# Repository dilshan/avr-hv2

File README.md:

AVR High Voltage Programmer 2
==========================

*AVR-HV2* is *Arduino* based high voltage parallel programmer for *[AVR](https://www.microchip.com/design-centers/8-bit/avr-mcus)* microcontrollers. This programmer can read, write, and erase both flash memory and EEPROM. Also, this can use to set fuse bits of *AVR* MCUs. 

*AVR-HV2* programmer is designed as an *[Arduino Mega](https://www.arduino.cc/en/Main/ArduinoBoardMega2560)* shield. Dimensions of the *AVR-HV2* are similar to the *Arduino Mega* board. It can be powered using a power source connected to the *Arduino Mega* board. The suggested power source for this programmer is a 12V 1A DC power adapter. 

The control software of this programmer is design to work on both *Windows* and *Linux* operating systems. It supports the import and export of memory data in the Intel hex file format. The communication link between the programmer and the control software is established through the USB port. 

The current firmware and control software of this programmer supports most of the generally available *AVR* MCUs which including *ATmega8*, *ATmega328*, *ATmega32*, *ATmega16*, etc. The *AVR* MCUs with extended addressing modes are currently not supported. 

The PCB board used in this project is sponsored by the *[PCBWay](https://www.pcbway.com/)*. PCB of this project can directly order from *PCBWay* through this [link](https://www.pcbway.com/project/shareproject/AVR_High_Voltage_Programmer_2.html).

This is a certified open-source hardware project. All the design files, [documentation](https://github.com/dilshan/avr-hv2/wiki) and firmware source code are available to [download](https://github.com/dilshan/avr-hv2/releases) at the project source repository. All the content of this project are distributed under the terms of the following license:

- Hardware License: [CC BY 4.0](https://creativecommons.org/licenses/by/4.0/)
- Software License: [MIT](https://github.com/dilshan/avr-hv2/blob/master/LICENSE)
- Documentation License: [CC BY 4.0](https://creativecommons.org/licenses/by/4.0/)

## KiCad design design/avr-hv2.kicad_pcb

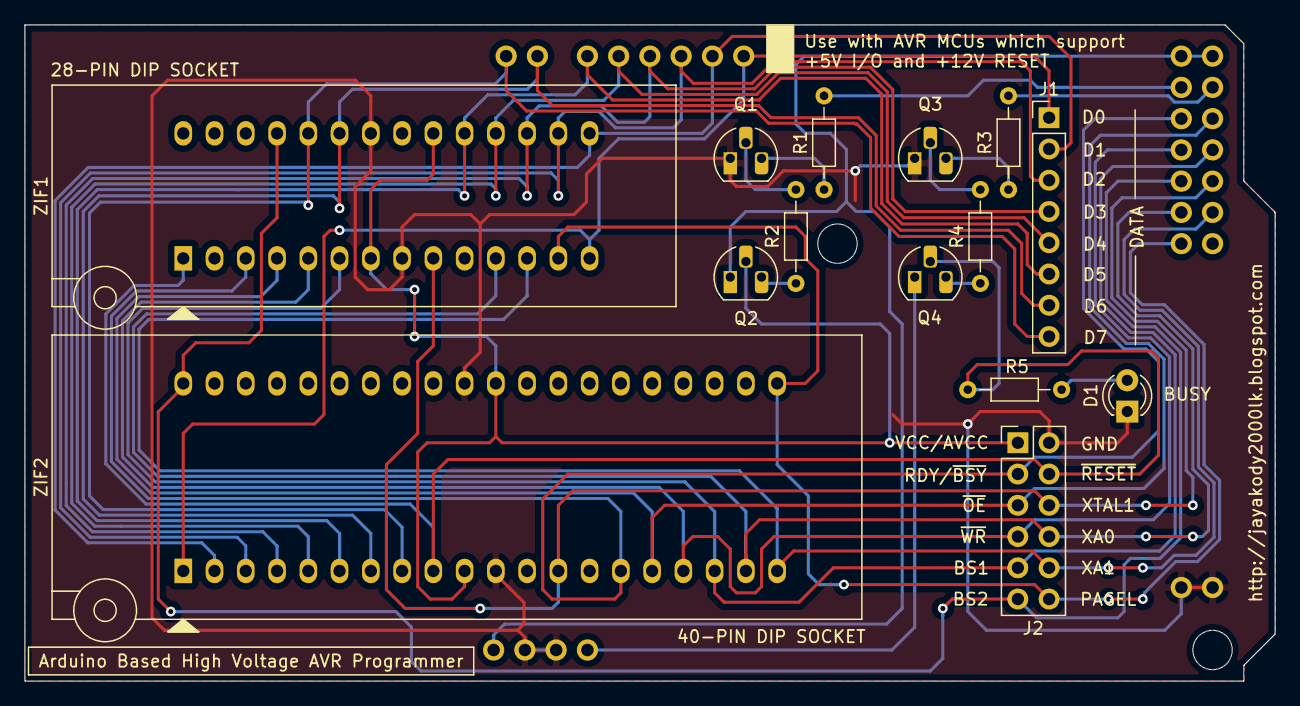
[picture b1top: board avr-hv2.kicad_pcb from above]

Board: 2 copper layers, 101.6 x 53.3 mm, 15 parts (0 on the bottom side), 31 nets.

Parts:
D1: LED (RED); LED_D3.0mm
J1: PROG-DATA1; PinHeader_1x08_P2.54mm_Vertical
J2: PROG-DATA2; PinHeader_2x06_P2.54mm_Vertical
Q1, Q3: 2SC945; TO-92_HandSolder
Q2, Q4: 2SA733; TO-92_HandSolder
R1, R3: 10K; R_Axial_DIN0204_L3.6mm_D1.6mm_P7.62mm_Horizontal
R2, R4: 220R; R_Axial_DIN0204_L3.6mm_D1.6mm_P7.62mm_Horizontal
R5: 4.7K; R_Axial_DIN0204_L3.6mm_D1.6mm_P7.62mm_Horizontal
XA1: Arduino Mega2560; MEGA2560
ZIF1: MCU-28; DIP_Socket-28_W6.9_W7.62_W10.16_W12.7_W13.5_3M_228-4817-00-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
ZIF2: MCU-40; DIP_Socket-40_W11.9_W12.7_W15.24_W17.78_W18.5_3M_240-1280-0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

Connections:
5V: Q2.1, XA1.5V1, XA1.5V3, XA1.5V4
12V: Q4.1, XA1.VIN
12V-CNT: R3.2, XA1.D23
BS1: J2.9, XA1.D27, ZIF1.6, ZIF2.18
BS2: J2.11, XA1.D28, ZIF1.25, ZIF2.40
D0: J1.1, XA1.D2, ZIF1.14, ZIF2.1
D1: J1.2, XA1.D3, ZIF1.15, ZIF2.2
D2: J1.3, XA1.D4, ZIF1.16, ZIF2.3
D3: J1.4, XA1.D5, ZIF1.17, ZIF2.4
D4: J1.5, XA1.D6, ZIF1.18, ZIF2.5
D5: J1.6, XA1.D7, ZIF1.19, ZIF2.6
D6: J1.7, XA1.D8, ZIF1.23, ZIF2.7
D7: J1.8, XA1.D9, ZIF1.24, ZIF2.8
GND: D1.1, J2.2, Q1.1, Q3.1, XA1.GND2, XA1.GND3, XA1.GND5, XA1.GND6, ZIF1.8, ZIF1.22, ZIF2.11, ZIF2.31
unnamed: D1.2, R5.1
unnamed: Q1.2, R2.2
unnamed: Q1.3, R1.1
unnamed: Q2.3, R2.1
unnamed: Q3.2, R4.2
unnamed: Q3.3, R3.1
unnamed: Q4.3, R4.1
OE: J2.5, XA1.D25, ZIF1.4, ZIF2.16
PAGEL: J2.12, XA1.D32, ZIF1.13, ZIF2.21
RDY: J2.3, XA1.D24, ZIF1.3, ZIF2.15
RESET: J2.4, Q4.2, R5.2, ZIF1.1, ZIF2.9
VCC: J2.1, Q2.2, ZIF1.7, ZIF1.20, ZIF2.10, ZIF2.30
VCC-CNT: R1.2, XA1.D22
WR: J2.7, XA1.D26, ZIF1.5, ZIF2.17
XA0: J2.8, XA1.D30, ZIF1.11, ZIF2.19
XA1: J2.10, XA1.D31, ZIF1.12, ZIF2.20
XTAL1: J2.6, XA1.D29, ZIF1.9, ZIF2.13

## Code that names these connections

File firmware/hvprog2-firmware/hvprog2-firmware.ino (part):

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#define PIN_VCC             22
#define PIN_12V             23

#define PIN_RDY             24
#define PIN_OE              25
#define PIN_WR              26
#define PIN_BS1             27
#define PIN_BS2             28
#define PIN_XTAL1           29
#define PIN_XA0             30
#define PIN_XA1             31
#define PIN_PAGEL           32

#define PIN_D0              2
#define PIN_D1              3
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#define PROG_ENABLE0        PIN_BS1
#define PROG_ENABLE1        PIN_XA0
#define PROG_ENABLE2        PIN_XA1
#define PROG_ENABLE3        PIN_PAGEL

#define loadAddressLow(a) loadAddress(LOW, a)
#define loadAddressHigh(a) loadAddress(HIGH, a)
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  digitalWrite(PIN_12V, LOW);

  // Reset command bits.
  digitalWrite(PIN_RDY, HIGH);
  digitalWrite(PIN_OE, LOW);
  digitalWrite(PIN_WR, LOW);
  digitalWrite(PIN_BS1, LOW);
  digitalWrite(PIN_BS2, LOW);
  digitalWrite(PIN_XTAL1, LOW);
  digitalWrite(PIN_XA0, LOW);
  digitalWrite(PIN_XA1, LOW);
  digitalWrite(PIN_PAGEL, LOW);
}

void loadCommand(unsigned char cmd)
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
  // Pulse XTAL1.
  delayMicroseconds(5);
  digitalWrite(PIN_XTAL1, HIGH);
  delayMicroseconds(5);
  digitalWrite(PIN_XTAL1, LOW);
  delayMicroseconds(5);
}

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
  // Pulse XTAL1.
  delayMicroseconds(5);
  digitalWrite(PIN_XTAL1, HIGH);
  delayMicroseconds(5);
  digitalWrite(PIN_XTAL1, LOW);
  delayMicroseconds(5);  
}

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
  // Pulse XTAL1.
  delayMicroseconds(5);
  digitalWrite(PIN_XTAL1, HIGH);
  delayMicroseconds(5);
  digitalWrite(PIN_XTAL1, LOW);
  delayMicroseconds(5);  
}

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
  // Pulse PAGEL.
  delayMicroseconds(5);
  digitalWrite(PIN_PAGEL, HIGH);
  delayMicroseconds(5);
  digitalWrite(PIN_PAGEL, LOW);
  delayMicroseconds(5);
}

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    delay(10);
    writeTimeout++;

    if(digitalRead(PIN_RDY) == HIGH)
    {
      writeTimeout = 0;
      break;      
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  delayMicroseconds(55);

  // Sep pin modes and initial values.
  pinMode(PIN_RDY, INPUT);
  pinMode(PIN_OE, OUTPUT);
  pinMode(PIN_WR, OUTPUT);
  pinMode(PIN_BS1, OUTPUT);
  pinMode(PIN_BS2, OUTPUT);
  pinMode(PIN_XTAL1, OUTPUT);
  pinMode(PIN_XA0, OUTPUT);
  pinMode(PIN_XA1, OUTPUT);
  pinMode(PIN_PAGEL, OUTPUT);

  setDataPinMode(OUTPUT);
  resetProgramMode();
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    delay(20);
    fuseSetTimeout++;

    if(digitalRead(PIN_RDY) == HIGH)
    {
      fuseSetTimeout = 0;
      break;      
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    delay(20);
    fuseSetTimeout++;

    if(digitalRead(PIN_RDY) == HIGH)
    {
      fuseSetTimeout = 0;
      break;      
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    delay(20);
    fuseSetTimeout++;

    if(digitalRead(PIN_RDY) == HIGH)
    {
      fuseSetTimeout = 0;
      break;      
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    delay(20);
    fuseSetTimeout++;

    if(digitalRead(PIN_RDY) == HIGH)
    {
      fuseSetTimeout = 0;
      break;      
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    delay(20);
    eraseTimeout++;

    if(digitalRead(PIN_RDY) == HIGH)
    {
      eraseTimeout = 0;
      break;      
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
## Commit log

2020-03-08 Initial version of the AVR-HV2.
2020-03-08 Update readme file with prototype image.
2020-03-08 Fixed issues in prototype photograph.
2020-03-10 Add support to configure individual fuse bytes.
2020-03-10 Fix typo in fuse configuration comment.
2020-03-12 Update readme file with documentation link.
2020-03-12 Add project license information.
2020-03-12 Update README.md
    Add PCBWay order link.
2020-03-13 Fix document error in license section.
2020-03-13 Fix minor issues in readme file.
2020-05-28 Add OSHW LK000007 mark.
2020-05-28 Add OSHWA certification mark and link.

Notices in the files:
firmware/hvprog2-firmware/hvprog2-firmware.ino:
Copyright (c) 2020 Dilshan R Jayakody [jayakody2000lk at gmail dot com]
design/avr-hv2.kicad_pcb:
This work is licensed under a Creative Commons
Attribution 4.0 International License.
